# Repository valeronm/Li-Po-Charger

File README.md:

# Li-Po-Charger
Schematic and PCB for Li-Po charger with power path, power management inputs, charging state and 3.3V output and I2C fuel gauge

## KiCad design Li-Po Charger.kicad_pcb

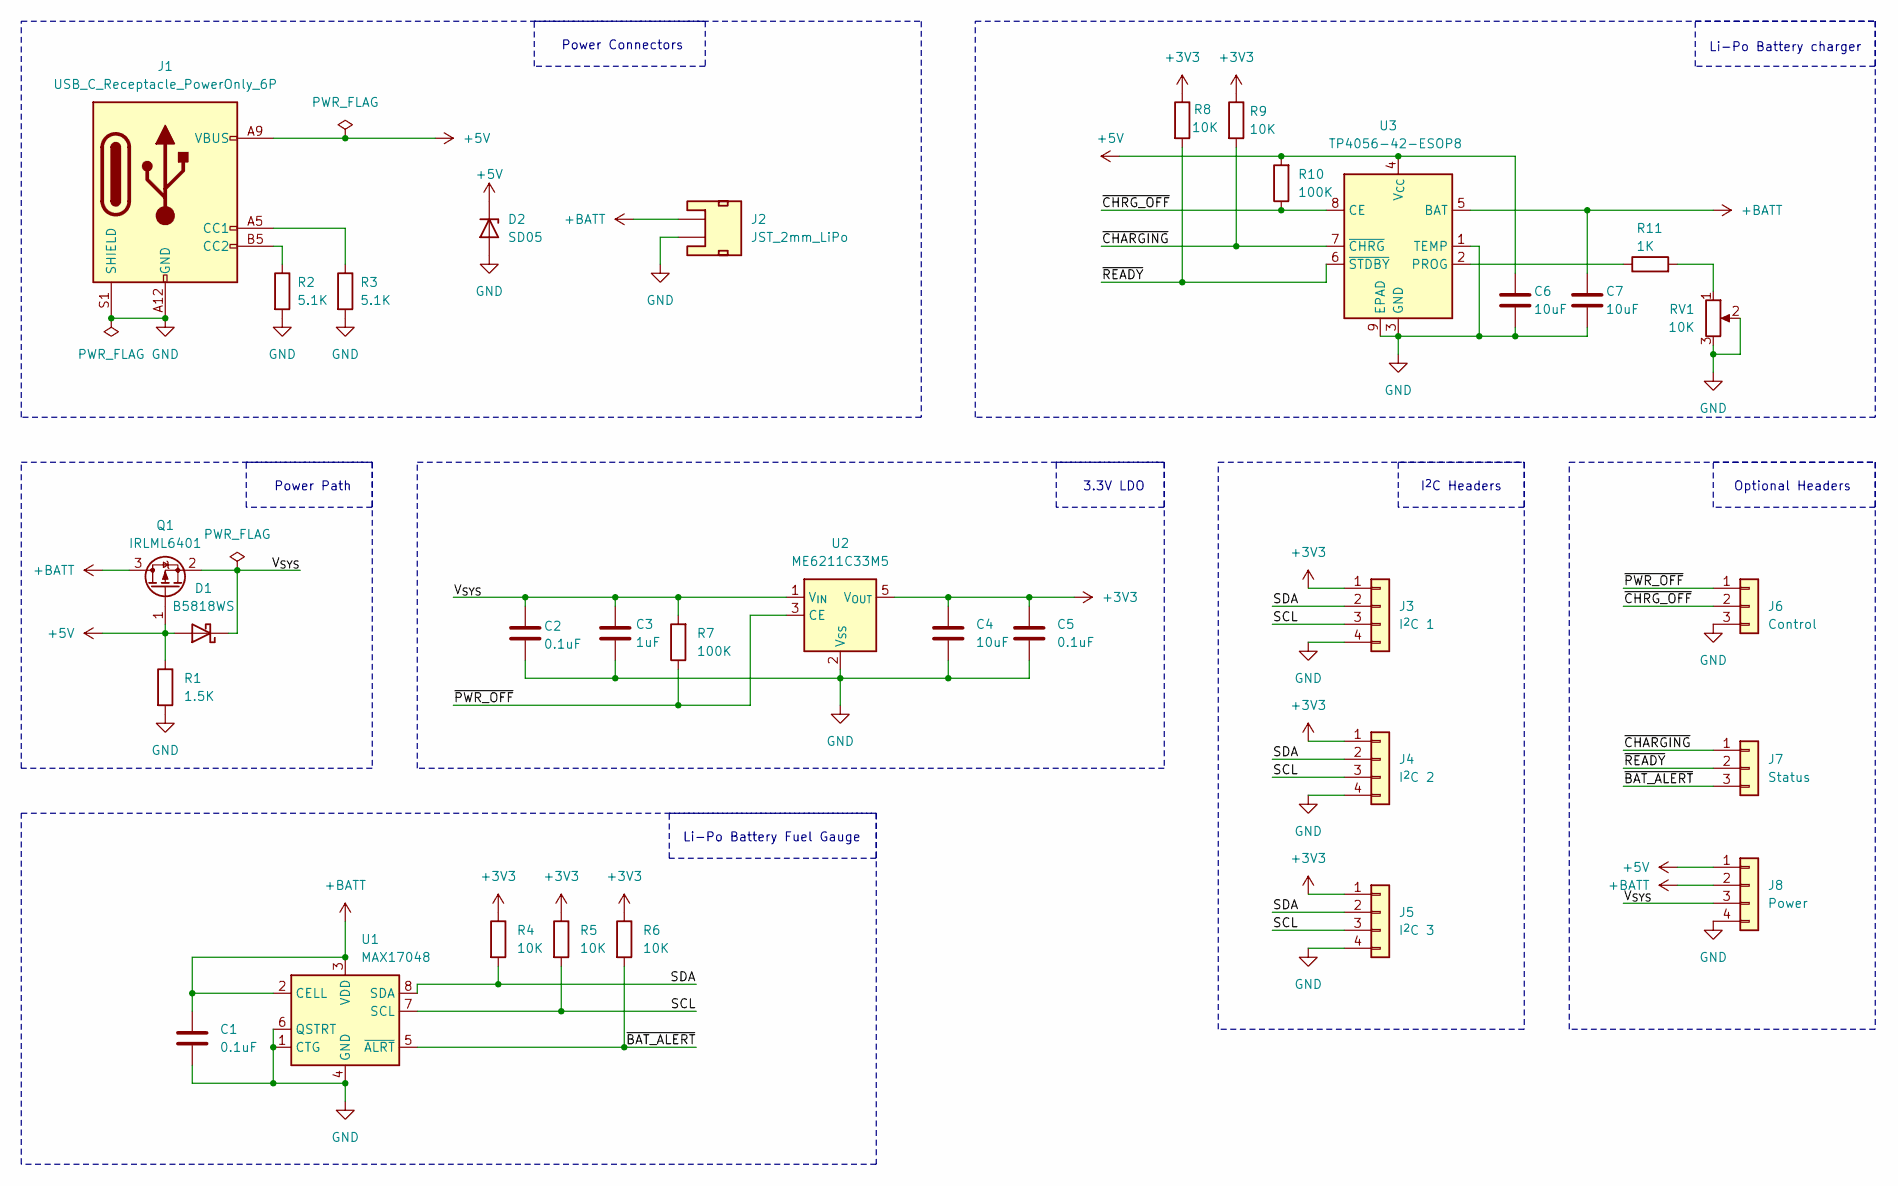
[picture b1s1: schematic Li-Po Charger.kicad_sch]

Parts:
C1, C2, C5: 0.1uF; C_0402_1005Metric
C3: 1uF; C_0603_1608Metric
C4, C6, C7: 10uF; C_0603_1608Metric
D1: B5818WS; D_SOD-323; LCSC Part # C22466361
D2: SD05; D_SOD-323; LCSC Part # C502527
J1: USB_C_Receptacle_PowerOnly_6P; USB_C_Receptacle_HRO_TYPE-C-31-M-17; LCSC Part # C283540
J2: JST_2mm_LiPo; JST_1x02_P2.0mm_Horizontal_SMD; LCSC Part # C295747
J3: I^{2}C 1; PinHeader_1x04_P2.54mm_Vertical
J4: I^{2}C 2; PinHeader_1x04_P2.54mm_Vertical
J5: I^{2}C 3; PinHeader_1x04_P2.54mm_Vertical
J6: Control; PinHeader_1x03_P2.54mm_Vertical
J7: Status; PinHeader_1x03_P2.54mm_Vertical
J8: Power; PinHeader_1x04_P2.54mm_Vertical
Q1: IRLML6401; SOT-23-3; LCSC Part # C382329
R1: 1.5K; R_0402_1005Metric
R2, R3: 5.1K; R_0402_1005Metric
R4, R5, R6, R8, R9: 10K; R_0402_1005Metric
R7, R10: 100K; R_0402_1005Metric
R11: 1K; R_0402_1005Metric
RV1: 10K; Potentiometer_Bourns_TC33X_Vertical; LCSC Part # C719176
U1: MAX17048; DFN-8-1EP_2x2mm_P0.5mm_EP0.8x1.6mm; LCSC Part # C2682616
U2: ME6211C33M5; SOT-23-5; LCSC Part # C82942
U3: TP4056-42-ESOP8; SOIC-8-1EP_3.9x4.9mm_P1.27mm_EP2.41x3.3mm; LCSC Part # C16581

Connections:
+3V3: C4.1, C5.1, J3.1, J4.1, J5.1, R4.1, R5.1, R6.1, R8.1, R9.1, U2.5 (V_{OUT})
+5V: C6.1, D1.2 (A), D2.1 (K), J1.A9 (VBUS), J1.B9 (VBUS), J8.1, Q1.1 (G), R1.1, R10.2, U3.4 (V_{CC})
+BATT: C1.1, C7.1, J2.2 (+), J8.2, Q1.3 (D), U1.2 (CELL), U1.3 (VDD), U3.5 (BAT)
/SCL: J3.3, J4.3, J5.3, R5.2, U1.7 (SCL)
/SDA: J3.2, J4.2, J5.2, R4.2, U1.8 (SDA)
/V_{SYS}: C2.1, C3.1, D1.1 (K), J8.3, Q1.2 (S), R7.2, U2.1 (V_{IN})
/~BAT_ALERT: J7.3, R6.2, U1.5 (~ALRT)
/~CHARGING: J7.1, R9.2, U3.7 (~CHRG)
/~CHRG_OFF: J6.2, R10.1, U3.8 (CE)
/~PWR_OFF: J6.1, R7.1, U2.3 (CE)
/~READY: J7.2, R8.2, U3.6 (~STDBY)
GND: C1.2, C2.2, C3.2, C4.2, C5.2, C6.2, C7.2, D2.2 (A), J1.A12 (GND), J1.B12 (GND), J1.S1 (SHIELD), J2.1 (-), J3.4, J4.4, J5.4, J6.3, J8.4, R1.2, R2.2, R3.2, RV1.2, RV1.3, U1.1 (CTG), U1.4 (GND), U1.6 (QSTRT), U1.9 (GND), U2.2 (V_{SS}), U3.1 (TEMP), U3.3 (GND), U3.9 (EPAD)
unnamed: J1.A5 (CC1), R3.1
unnamed: J1.B5 (CC2), R2.1
unnamed: R11.2, RV1.1
unnamed: R11.1, U3.2 (PROG)

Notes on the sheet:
Optional Headers
Li-Po Battery Fuel Gauge
Power Connectors
Li-Po Battery charger
3.3V LDO
I^{2}C Headers
Power Path

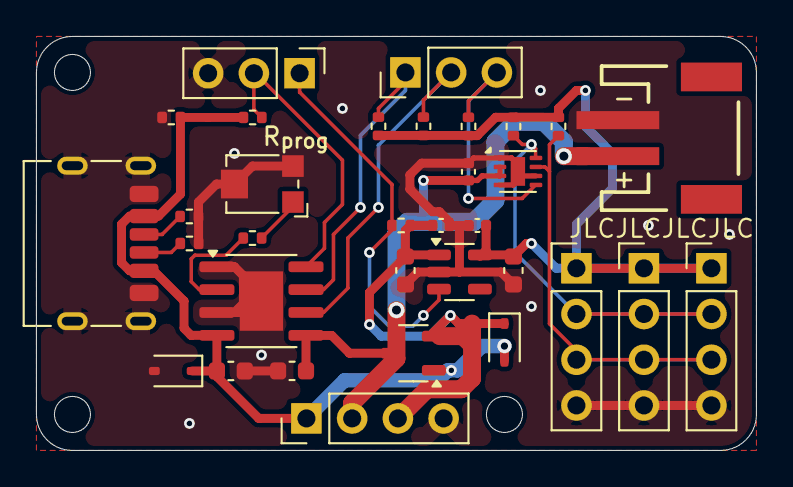
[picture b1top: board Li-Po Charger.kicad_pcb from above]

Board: 2 copper layers, 40.0 x 23.0 mm, 33 parts (0 on the bottom side), 16 nets.

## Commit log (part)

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2025-09-24 Initial revision
